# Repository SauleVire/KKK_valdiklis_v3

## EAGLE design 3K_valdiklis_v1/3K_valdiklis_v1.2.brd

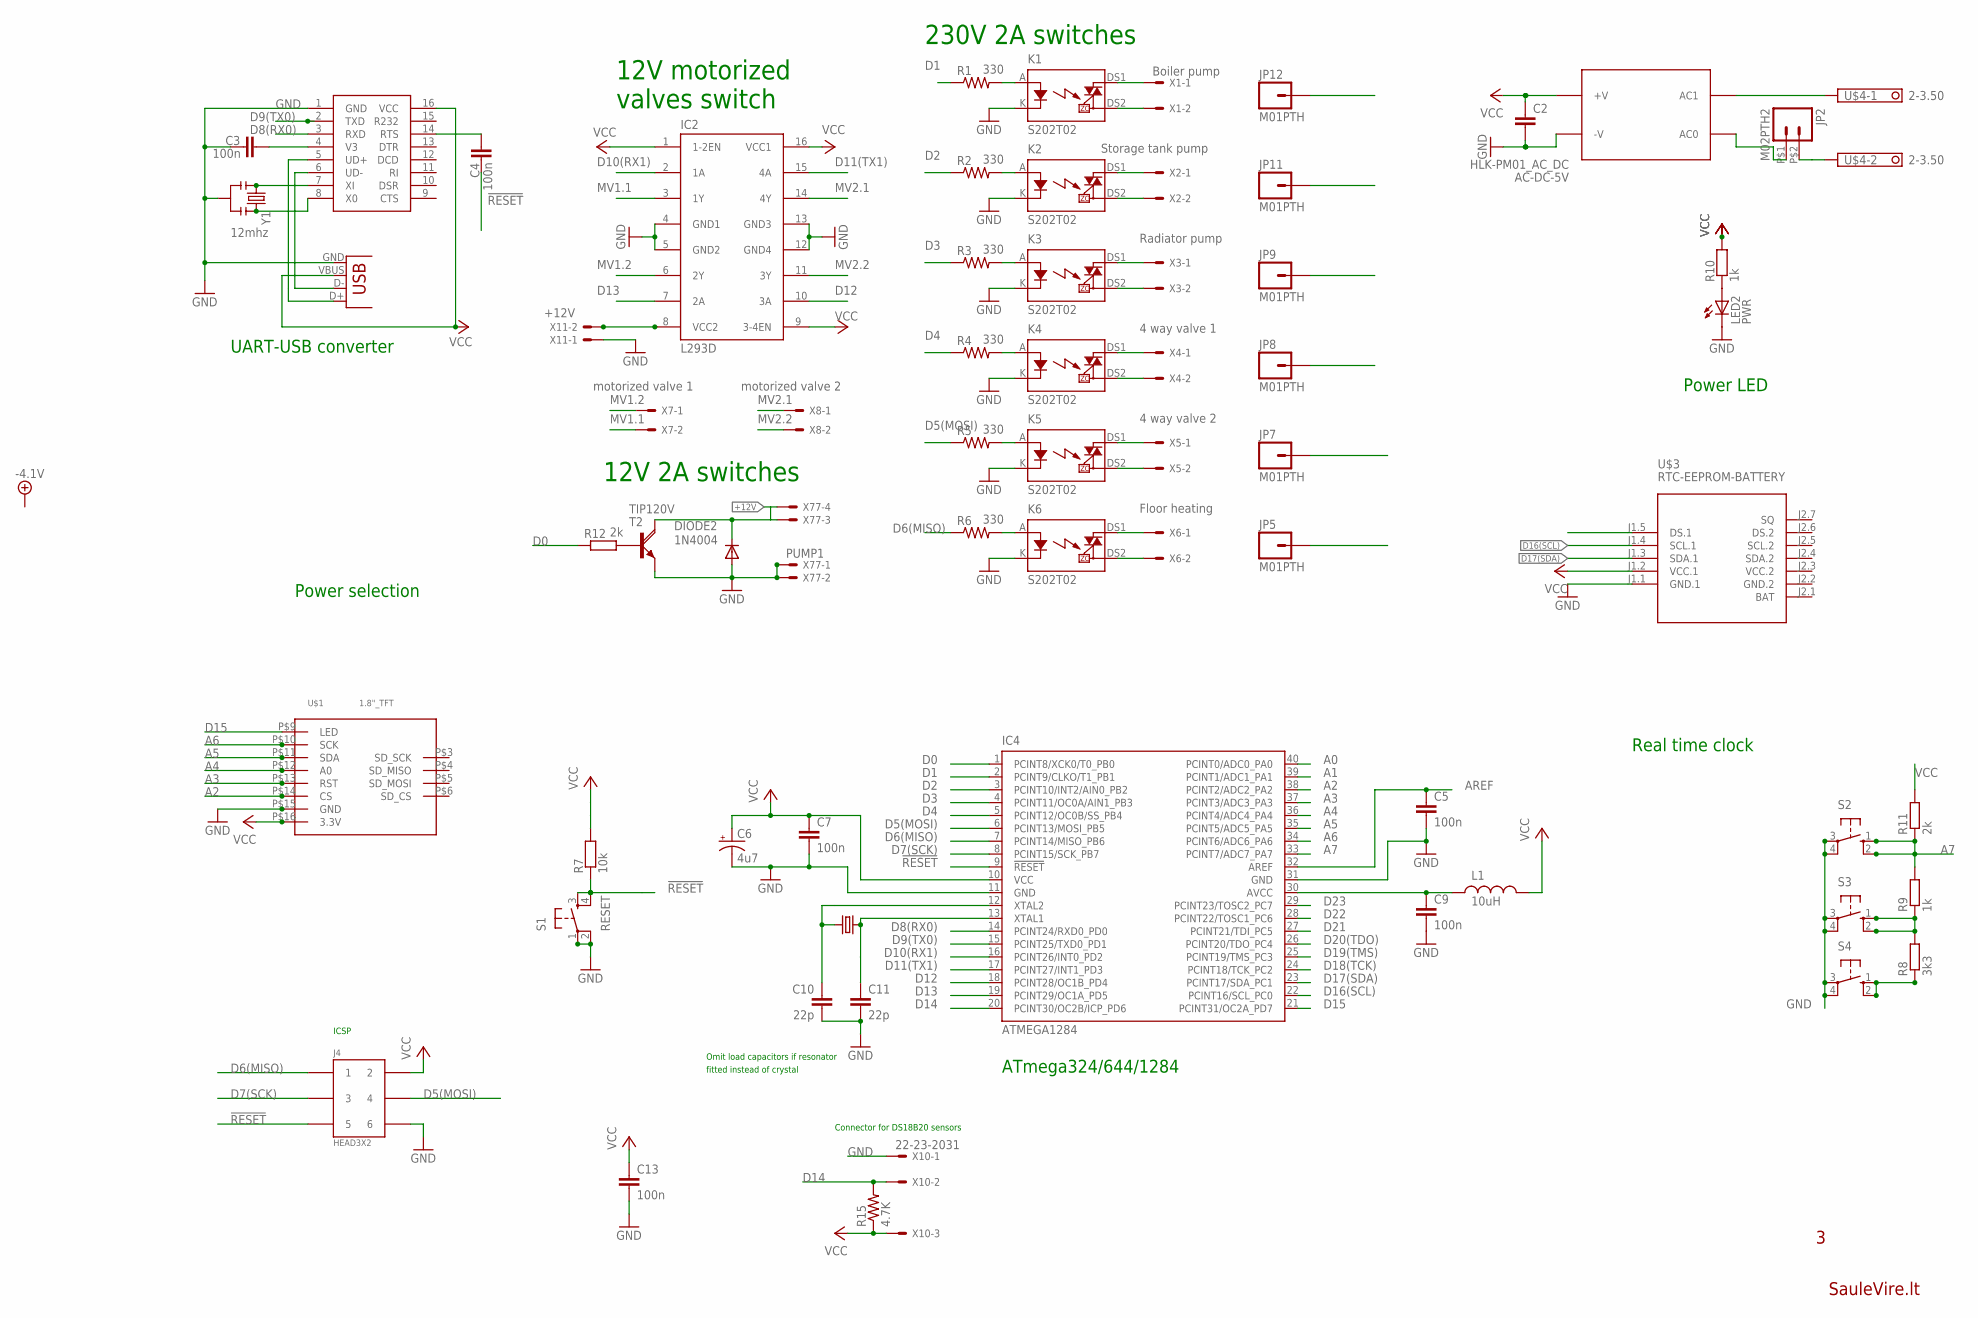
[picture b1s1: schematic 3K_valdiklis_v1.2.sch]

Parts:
AC-DC-5V: HLK-PM01_AC_DC
C2: C-EU025-024X044; C025-024X044
C3, C4, C5, C7, C9, C13: 100n; CAP-PTH-SMALL
C6: 4u7; CPOL-RADIAL-10UF-25V
C10, C11: 22p; CAP-PTH-SMALL
DIODE2: 1N4004; DO41-10
IC2: L293D; DIL16
IC4: ATMEGA1284; DIL40
J4: HEAD3X2
JP2: M02PTH2; 1X02_BIG
JP3: USB-B; USB-B-PTH
JP5, JP7, JP8, JP9, JP11, JP12: M01PTH; 1X01
K1, K2, K3, K4, K5, K6: S202T02
L1: 10uH; RES-AXIAL-0.4
LED2: PWR; LED3MM
R1, R2, R3, R4, R5, R6: 330; 0207/10
R7: 10k; RES-AXIAL-0.4
R8: 3k3; 0207/10
R9: 1k; 0207/10
R10: 1k; RES-AXIAL-0.4
R11, R12: 2k; 0207/10
R15: 4.7K; 0207/10
S1: RESET; TACTILE-PTH
S2, S3, S4: 10-XX; B3F-10XX
T2: TIP120V; TO220AV
U$1: 1.8"_TFT
U$2: CH340G; SO016
U$3: RTC-EEPROM-BATTERY; RTC_EEPROM_BATTERY
U$4: 2-3.50
X1: Boiler pump; 22-23-2021
X2: Storage tank pump; 22-23-2021
X3: Radiator pump; 22-23-2021
X4: 4 way valve 1; 22-23-2021
X5: 4 way valve 2; 22-23-2021
X6: Floor heating; 22-23-2021
X7: motorized valve 1; 22-23-2021
X8: motorized valve 2; 22-23-2021
X9: 16MHz; HC49US
X10: 22-23-2031
X11: +12V; 22-23-2021
X77: PUMP1; 22-23-2041
Y1: 12mhz; RESONATOR-PTH

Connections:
220V: AC-DC-5V.AC1, U$4.1
!RESET: C4.1, IC4.9 (!RESET), J4.5, R7.P$1 (1), S1.3, S1.4
+12V: DIODE2.C, T2.C, X77.3, X77.4
A0: IC4.40 (PCINT0/ADC0_PA0)
A1: IC4.39 (PCINT1/ADC1_PA1)
A2: IC4.38 (PCINT2/ADC2_PA2), U$1.P$14 (CS)
A3: IC4.37 (PCINT3/ADC3_PA3), U$1.P$13 (RST)
A4: IC4.36 (PCINT4/ADC4_PA4), U$1.P$12 (A0)
A5: IC4.35 (PCINT5/ADC5_PA5), U$1.P$11 (SDA)
A6: IC4.34 (PCINT6/ADC6_PA6), U$1.P$10 (SCK)
A7: IC4.33 (PCINT7/ADC7_PA7), R9.2, R11.1, S2.1 (S), S2.2 (S1)
AREF: C5.1, IC4.32 (AREF)
AVCC: C9.1, IC4.30 (AVCC), L1.P$1 (1)
D0: IC4.1 (PCINT8/XCK0/T0_PB0), R12.1
D1: IC4.2 (PCINT9/CLKO/T1_PB1), R1.1
D2: IC4.3 (PCINT10/INT2/AIN0_PB2), R2.1
D3: IC4.4 (PCINT11/OC0A/AIN1_PB3), R3.1
D4: IC4.5 (PCINT12/OC0B/SS_PB4), R4.1
D5(MOSI): IC4.6 (PCINT13/MOSI_PB5), J4.4, R5.1
D6(MISO): IC4.7 (PCINT14/MISO_PB6), J4.1, R6.1
D7(SCK): IC4.8 (PCINT15/SCK_PB7), J4.3
D8(RX0): IC4.14 (PCINT24/RXD0_PD0), U$2.3 (RXD)
D9(TX0): IC4.15 (PCINT25/TXD0_PD1), U$2.2 (TXD)
D10(RX1): IC2.2 (1A), IC4.16 (PCINT26/INT0_PD2)
D11(TX1): IC2.15 (4A), IC4.17 (PCINT27/INT1_PD3)
D12: IC2.10 (3A), IC4.18 (PCINT28/OC1B_PD4)
D13: IC2.7 (2A), IC4.19 (PCINT29/OC1A_PD5)
D14: IC4.20 (PCINT30/OC2B/ICP_PD6), R15.2, X10.2
D15: IC4.21 (PCINT31/OC2A_PD7), U$1.P$9 (LED)
D16(SCL): IC4.22 (PCINT16/SCL_PC0), U$3.J1.4 (SCL.1)
D17(SDA): IC4.23 (PCINT17/SDA_PC1), U$3.J1.3 (SDA.1)
D18(TCK): IC4.24 (PCINT18/TCK_PC2)
D19(TMS): IC4.25 (PCINT19/TMS_PC3)
D20(TDO): IC4.26 (PCINT20/TDO_PC4)
D21: IC4.27 (PCINT21/TDI_PC5)
D22: IC4.28 (PCINT22/TOSC1_PC6)
D23: IC4.29 (PCINT23/TOSC2_PC7)
GND: AC-DC-5V.-V, C2.2, C3.1, C5.2, C6.2 (-), C7.2, C9.2, C10.2, C11.2, C13.2, DIODE2.A, IC2.4 (GND1), IC2.5 (GND2), IC2.12 (GND4), IC2.13 (GND3), IC4.11 (GND), IC4.31 (GND), J4.6, JP3.GND, K1.K, K2.K, K3.K, K4.K, K5.K, K6.K, LED2.K (C), S1.1, S1.2, S2.3, S2.4 (P1), S3.3, S3.4 (P1), S4.3, S4.4 (P1), T2.E, U$1.P$15 (GND), U$2.1 (GND), U$3.J1.1 (GND.1), X10.1, X11.1, X77.1, X77.2, Y1.2
GND.2: U$3.J2.2 (GND.2)
MV1.1: IC2.3 (1Y), X7.2
MV1.2: IC2.6 (2Y), X7.1
MV2.1: IC2.14 (4Y), X8.1
MV2.2: IC2.11 (3Y), X8.2
unnamed: C11.1, IC4.13 (XTAL1), X9.1
unnamed: C10.1, IC4.12 (XTAL2), X9.2
unnamed: AC-DC-5V.AC0, JP2.P$1 (1)
unnamed: JP2.P$2 (2), U$4.2
unnamed: R8.1, S4.1 (S), S4.2 (S1)
unnamed: U$2.7 (XI), Y1.1
unnamed: LED2.A, R10.P$1 (1)
unnamed: U$2.8 (X0), Y1.3
unnamed: R8.2, R9.1, S3.1 (S), S3.2 (S1)
unnamed: C4.2, U$2.14 (RTS)
unnamed: JP3.D-, U$2.6 (UD-)
unnamed: R12.2, T2.B
unnamed: C3.2, U$2.4 (V3)
unnamed: K3.A, R3.2
unnamed: JP9.1, K3.DS1, X3.1
unnamed: IC2.8 (VCC2), X11.2
unnamed: JP3.D+, U$2.5 (UD+)
unnamed: K3.DS2, X3.2
unnamed: K2.A, R2.2
unnamed: JP11.1, K2.DS1, X2.1
unnamed: K2.DS2, X2.2
unnamed: K4.A, R4.2
unnamed: JP8.1, K4.DS1, X4.1
unnamed: K4.DS2, X4.2
unnamed: K1.A, R1.2
unnamed: JP12.1, K1.DS1, X1.1
unnamed: K1.DS2, X1.2
unnamed: K6.A, R6.2
unnamed: JP5.1, K6.DS1, X6.1
unnamed: K6.DS2, X6.2
unnamed: K5.A, R5.2
unnamed: JP7.1, K5.DS1, X5.1
unnamed: K5.DS2, X5.2
VCC: AC-DC-5V.+V, C2.1, C6.1 (+), C7.1, C13.1, IC2.1 (1-2EN), IC2.9 (3-4EN), IC2.16 (VCC1), IC4.10 (VCC), J4.2, JP3.VBUS, L1.P$2 (2), R7.P$2 (2), R10.P$2 (2), R11.2, R15.1, U$1.P$16 (3.3V), U$2.16 (VCC), U$3.J1.2 (VCC.1), X10.3
VCC.2: U$3.J2.3 (VCC.2)

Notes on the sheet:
Real time clock
ATmega324/644/1284
Power selection
Power LED
SauleVire.lt
Omit load capacitors if resonator
fitted instead of crystal
Connector for DS18B20 sensors
230V 2A switches
12V motorized valves switch
12V 2A switches
ICSP
UART-USB converter

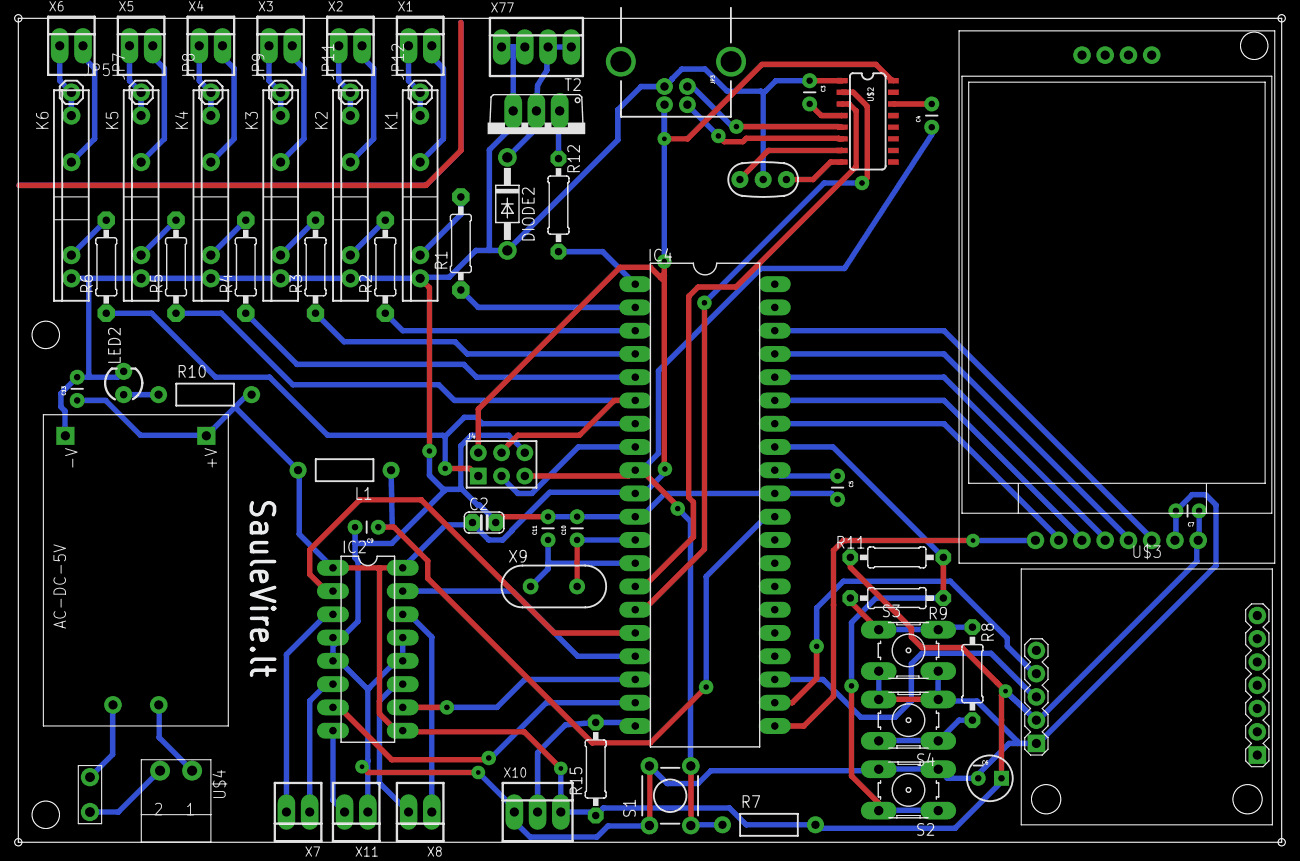
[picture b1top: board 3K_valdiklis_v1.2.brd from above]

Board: 2 copper layers, 138.0 x 90.0 mm, 66 parts (0 on the bottom side), 68 nets.

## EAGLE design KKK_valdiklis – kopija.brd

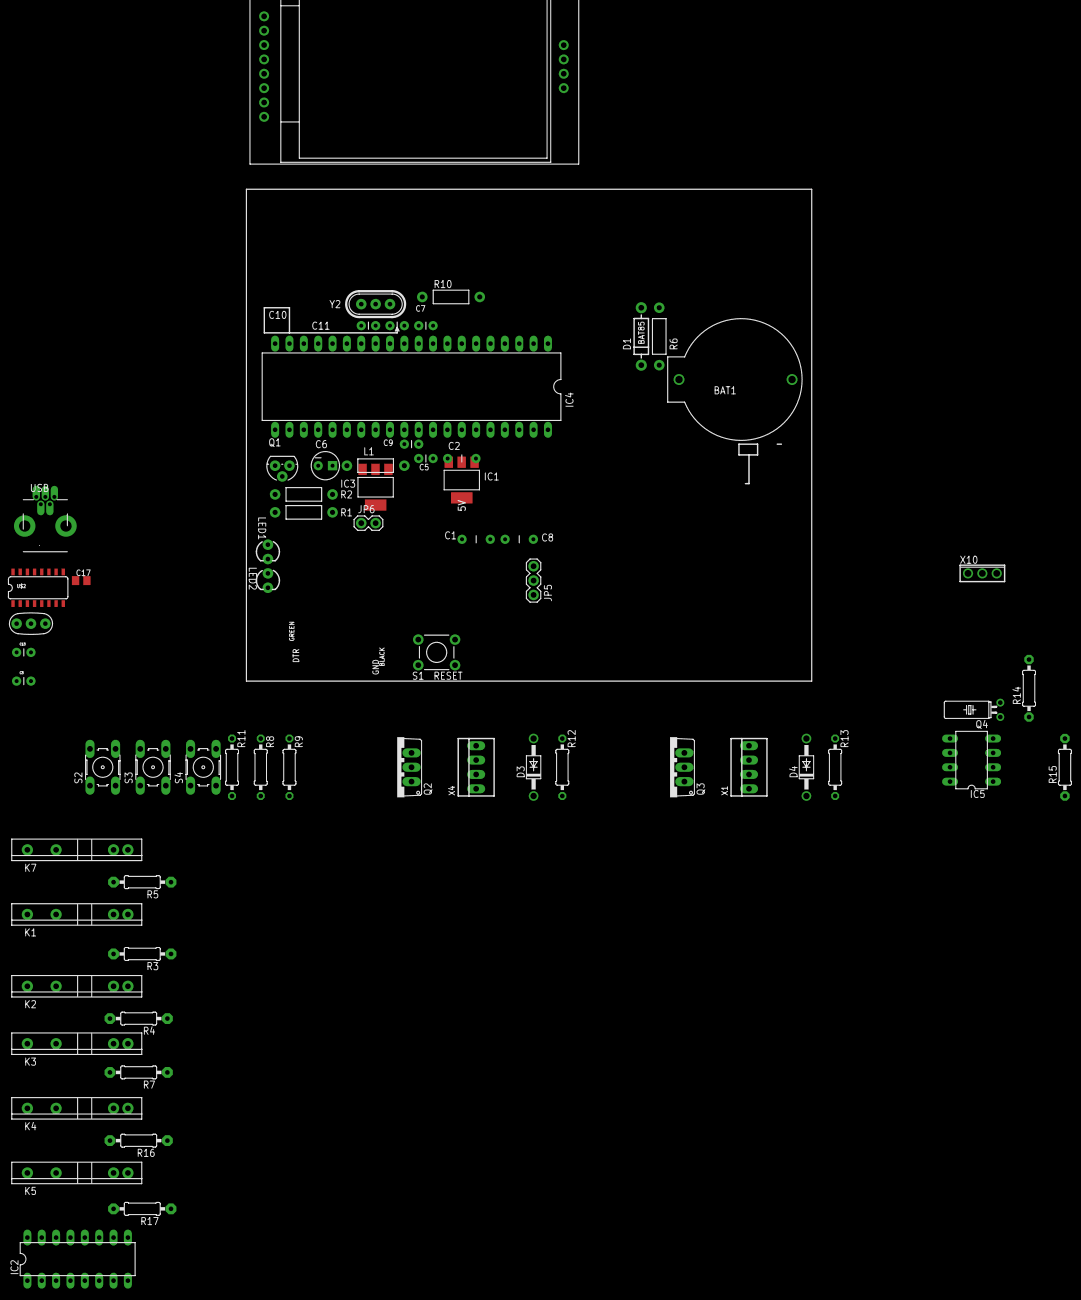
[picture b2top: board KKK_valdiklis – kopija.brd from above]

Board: 2 copper layers, 100.0 x 87.0 mm, 65 parts (0 on the bottom side), 45 nets, no tracks yet.

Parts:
BAT1: CR2032; BATTCOM_20MM_PTH
C1, C2, C8: 1u; CAP-PTH-5MM
C3, C5, C7, C9, C13: 100n; CAP-PTH-SMALL
C6: 4u7; CPOL-RADIAL-10UF-25V
C10, C11: 22p; CAP-PTH-SMALL
C17: 0.1uF; C0805K
D1: BAT85; DIODE-TH-0.4
D3, D4: 1N4004; DO41-10
IC1: MCP1702-3.3; SOT223
IC2: L293D; DIL16
IC3: MCP1702-5.0; SOT223
IC4: ATMEGA1284; DIL40
IC5: DS1307; DIL08
JP5: 3V3/5V; 1X03
JP6: VREG PWR; 1X02
K1, K2, K3, K4, K5, K7: S202T02
L1: 10uH; RES-AXIAL-0.4
LED1: D13; LED3MM
LED2: PWR; LED3MM
Q1: 2N7000; TO-92
Q2, Q3: TIP120V; TO220AV
Q4: 32.768; TC38H
R1, R2: 1k; RES-AXIAL-0.4
R3, R4, R5, R7, R16, R17: 330; 0207/10
R6: 10k; RES-AXIAL-0.4
R8: 3k3; 0207/10
R9: 1k; 0207/10
R10: 1M; RES-AXIAL-0.4
R11, R12, R13: 2k; 0207/10
R14: 2.2K; 0207/10
R15: 2.2k; 0207/10
S1: RESET; TACTILE-PTH
S2, S3, S4: B3F-10XX
U$1: 1.8"_TFT
U$2: CH340G; SO016
USB: USB-MINIB-THM-MOLEX
X1, X4: PUMP; 22-23-2041
X10: 3POL254
Y1: 12mhz; RESONATOR-PTH
Y2: 16MHz; HC49U-V-RESONATOR

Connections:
13(SCK): Q1.2, R10.P$2
20(SDA): IC5.5, R15.1
21(SCL): IC5.6, R14.2
!RESET: C17.2, D1.A, IC4.9, R6.P$1, S1.3, S1.4
+3V3: C2.1, IC1.2, JP5.1
+5V: C1.1, IC1.3, JP5.3, JP6.2, U$2.16, USB.VBUS, X10.3
A0: IC4.40, R9.2, R11.1, S2.1, S2.2
AREF: C5.1, IC4.32
AVCC: C9.1, IC4.30, L1.P$1
D0: IC4.1, R5.1
D1: IC4.2, R17.1
D2: IC4.3, R16.1, X10.2
D3: IC4.4, R7.1, R12.1, R13.1
D4: IC4.5, R4.1
GND: BAT1.2, C1.2, C2.2, C3.1, C5.2, C6.2, C7.2, C8.2, C9.2, C10.2, C11.2, C13.2, D3.A, IC1.1, IC3.1, IC4.11, IC4.31, IC5.4, K1.K, K2.K, K3.K, K4.K, K5.K, K7.K, LED2.K, Q1.1, Q2.E, R10.P$1, S1.1, S1.2, S2.3, S2.4, S3.3, S3.4, S4.3, S4.4, U$2.1, USB.GND, USB.ID, X4.3, X4.4, X10.1, Y1.2, Y2.GND
GND1: D4.A, IC2.4, Q3.E, X1.3, X1.4
unnamed: C11.1, IC4.13, Y2.2
unnamed: C10.1, IC4.12, Y2.1
unnamed: LED1.A, R1.P$1
unnamed: LED1.K, Q1.3
unnamed: U$2.7, Y1.1
unnamed: R8.1, S4.1, S4.2
unnamed: C3.2, U$2.4
unnamed: LED2.A, R2.P$1
unnamed: U$2.8, Y1.3
unnamed: R8.2, R9.1, S3.1, S3.2
unnamed: C17.1, U$2.14
unnamed: U$2.6, USB.D-
unnamed: Q2.B, R12.2
unnamed: IC3.2, JP6.1
unnamed: D3.C, Q2.C, X4.1, X4.2
unnamed: K1.A, R3.2
unnamed: Q3.B, R13.2
unnamed: D4.C, Q3.C, X1.1, X1.2
unnamed: IC5.1, Q4.2
unnamed: IC5.2, Q4.1
unnamed: U$2.5, USB.D+
unnamed: K2.A, R4.2
unnamed: BAT1.1, IC5.3
unnamed: K7.A, R5.2
unnamed: K3.A, R7.2
unnamed: K4.A, R16.2
unnamed: K5.A, R17.2
VCC: C6.1, C7.1, C13.1, D1.C, IC4.10, IC5.8, JP5.2, L1.P$2, R1.P$2, R2.P$2, R6.P$2, R11.2, R14.1, R15.2
VIN: C8.1, IC3.3

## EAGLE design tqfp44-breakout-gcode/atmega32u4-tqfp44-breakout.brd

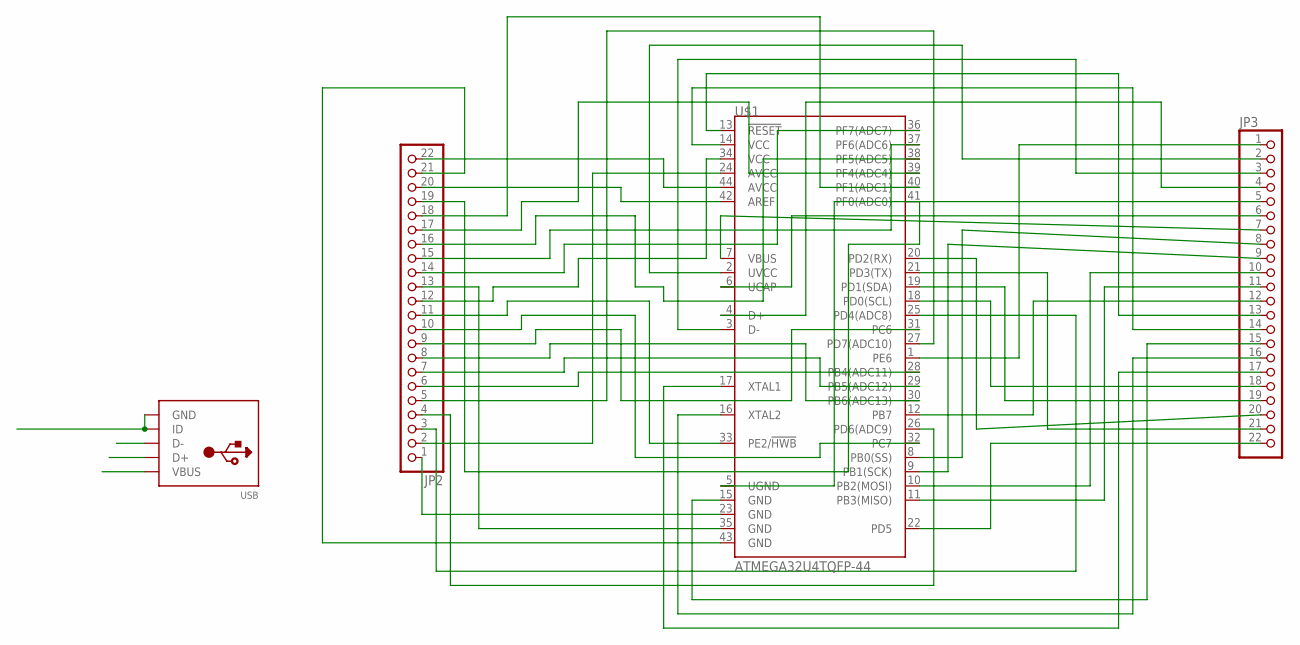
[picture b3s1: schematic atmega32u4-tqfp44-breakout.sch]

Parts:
JP2, JP3: PINHD-1X22; 1X22
U$1: ATMEGA32U4TQFP-44; TQFP44
USB: USB-MINIB-THM-MOLEX

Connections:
D+: JP3.4, U$1.4 (D+)
D-: JP3.3, U$1.3 (D-)
GND1: USB.GND, USB.ID
unnamed: JP3.1, U$1.1 (PE6)
unnamed: JP2.2, U$1.24 (AVCC)
unnamed: JP3.5, U$1.5 (UGND)
unnamed: JP3.6, U$1.6 (UCAP)
unnamed: JP3.7, U$1.7 (VBUS)
unnamed: JP3.8, U$1.8 (PB0(SS))
unnamed: JP3.9, U$1.9 (PB1(SCK))
unnamed: JP3.10, U$1.10 (PB2(MOSI))
unnamed: JP3.11, U$1.11 (PB3(MISO))
unnamed: JP3.12, U$1.12 (PB7)
unnamed: JP3.13, U$1.13 (!RESET)
unnamed: JP3.14, U$1.14 (VCC)
unnamed: JP3.15, U$1.15 (GND)
unnamed: JP3.16, U$1.16 (XTAL2)
unnamed: JP3.17, U$1.17 (XTAL1)
unnamed: JP3.18, U$1.18 (PD0(SCL))
unnamed: JP3.19, U$1.19 (PD1(SDA))
unnamed: JP3.20, U$1.20 (PD2(RX))
unnamed: JP3.21, U$1.21 (PD3(TX))
unnamed: JP3.22, U$1.22 (PD5), USB.D-
unnamed: JP2.1, U$1.23 (GND), USB.D+
unnamed: JP2.22, U$1.44 (AVCC)
unnamed: JP2.3, U$1.25 (PD4(ADC8))
unnamed: JP3.2, U$1.2 (UVCC)
unnamed: JP2.4, U$1.26 (PD6(ADC9))
unnamed: JP2.5, U$1.27 (PD7(ADC10))
unnamed: JP2.6, U$1.28 (PB4(ADC11))
unnamed: JP2.7, U$1.29 (PB5(ADC12))
unnamed: JP2.8, U$1.30 (PB6(ADC13))
unnamed: JP2.9, U$1.31 (PC6)
unnamed: JP2.10, U$1.32 (PC7)
unnamed: JP2.11, U$1.33 (PE2/!HWB)
unnamed: JP2.12, U$1.34 (VCC)
unnamed: JP2.13, U$1.35 (GND)
unnamed: JP2.14, U$1.36 (PF7(ADC7))
unnamed: JP2.15, U$1.37 (PF6(ADC6))
unnamed: JP2.16, U$1.38 (PF5(ADC5))
unnamed: JP2.17, U$1.39 (PF4(ADC4))
unnamed: JP2.18, U$1.40 (PF1(ADC1))
unnamed: JP2.19, U$1.41 (PF0(ADC0))
unnamed: JP2.20, U$1.42 (AREF)
unnamed: JP2.21, U$1.43 (GND)
VCC: USB.VBUS

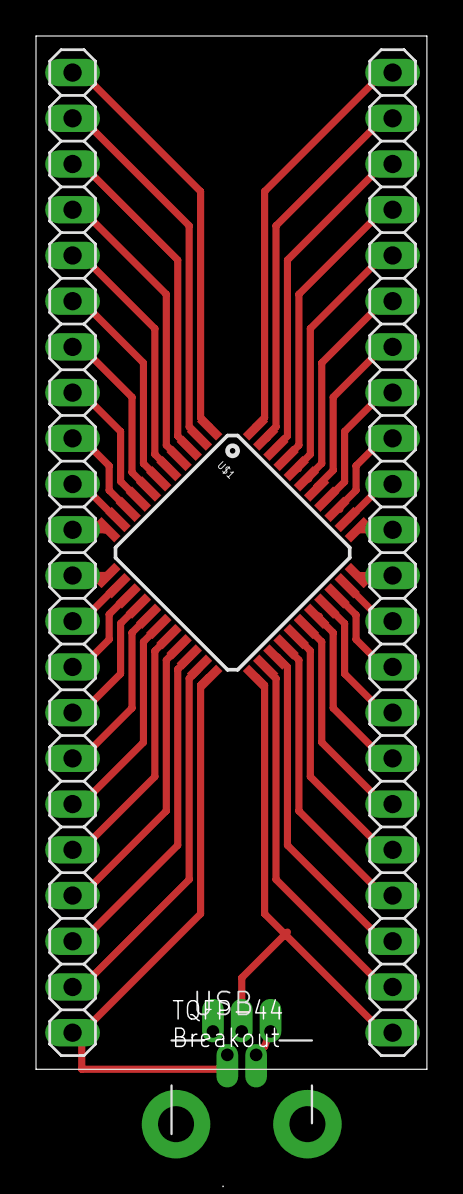
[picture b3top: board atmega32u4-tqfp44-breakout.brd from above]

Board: 2 copper layers, 21.7 x 57.4 mm, 4 parts (0 on the bottom side), 45 nets.

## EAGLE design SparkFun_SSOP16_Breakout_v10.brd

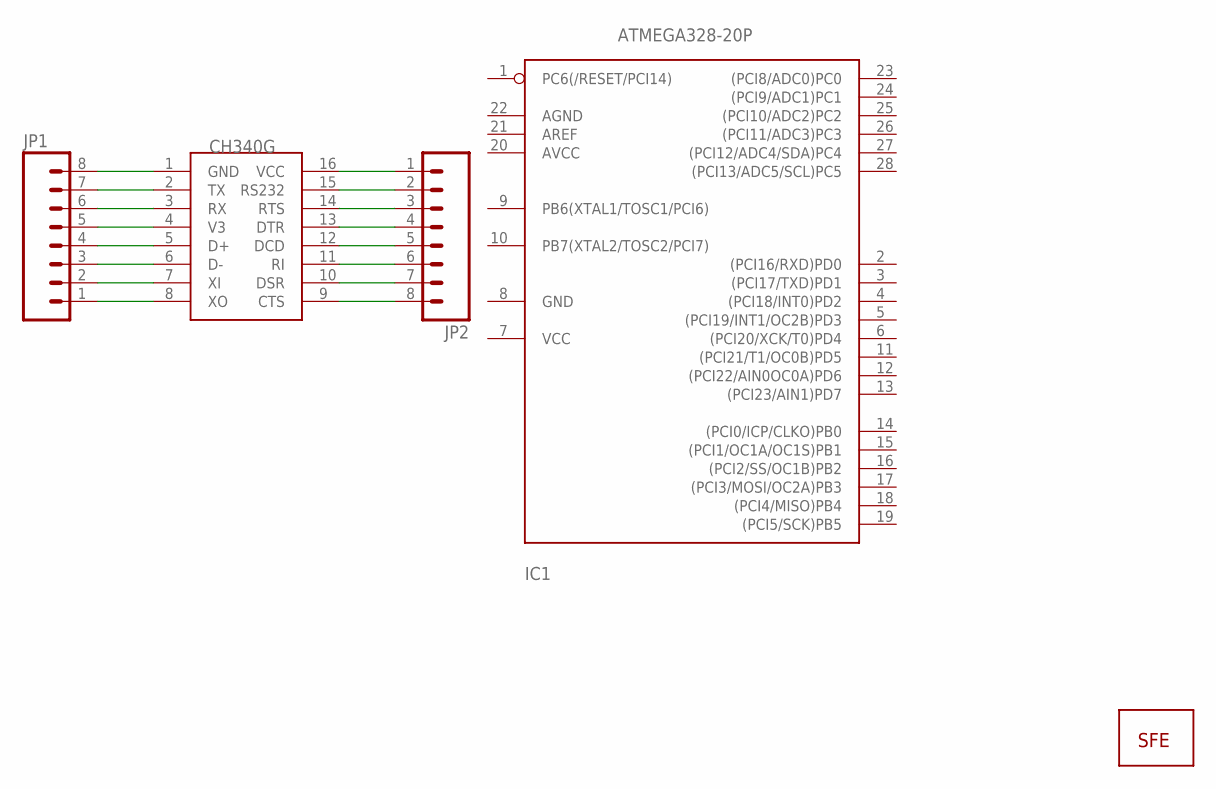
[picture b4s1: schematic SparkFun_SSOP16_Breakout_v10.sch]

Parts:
IC1: ATMEGA328-20P; DIL28-3
JP1, JP2: M08; 1X08
U$1: LOGO-SFESK; SFE-LOGO-FLAME
U$2: CH340G; SOIC16

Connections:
unnamed: JP1.1, U$2.8 (XO)
unnamed: JP1.2, U$2.7 (XI)
unnamed: JP1.3, U$2.6 (D-)
unnamed: JP1.4, U$2.5 (D+)
unnamed: JP1.5, U$2.4 (V3)
unnamed: JP1.6, U$2.3 (RX)
unnamed: JP1.7, U$2.2 (TX)
unnamed: JP1.8, U$2.1 (GND)
unnamed: JP2.1, U$2.16 (VCC)
unnamed: JP2.2, U$2.15 (RS232)
unnamed: JP2.3, U$2.14 (RTS)
unnamed: JP2.4, U$2.13 (DTR)
unnamed: JP2.5, U$2.12 (DCD)
unnamed: JP2.6, U$2.11 (RI)
unnamed: JP2.7, U$2.10 (DSR)
unnamed: JP2.8, U$2.9 (CTS)

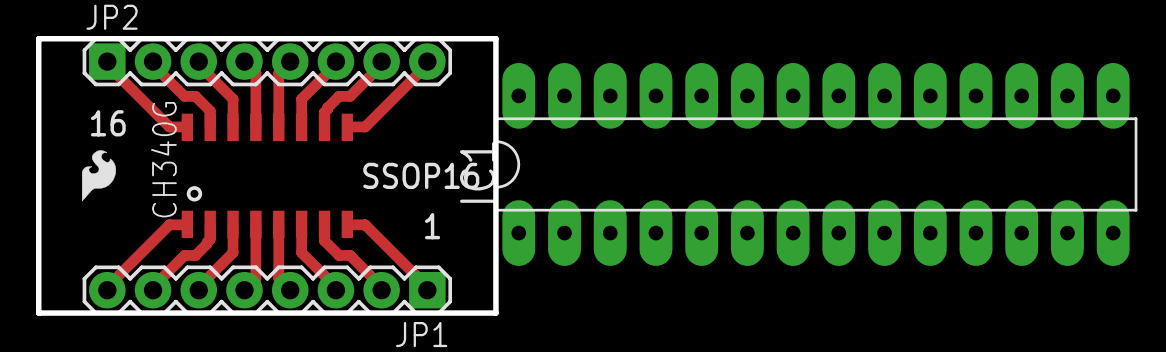
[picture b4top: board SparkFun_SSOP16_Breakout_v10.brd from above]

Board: 2 copper layers, 25.4 x 15.2 mm, 5 parts (0 on the bottom side), 16 nets.

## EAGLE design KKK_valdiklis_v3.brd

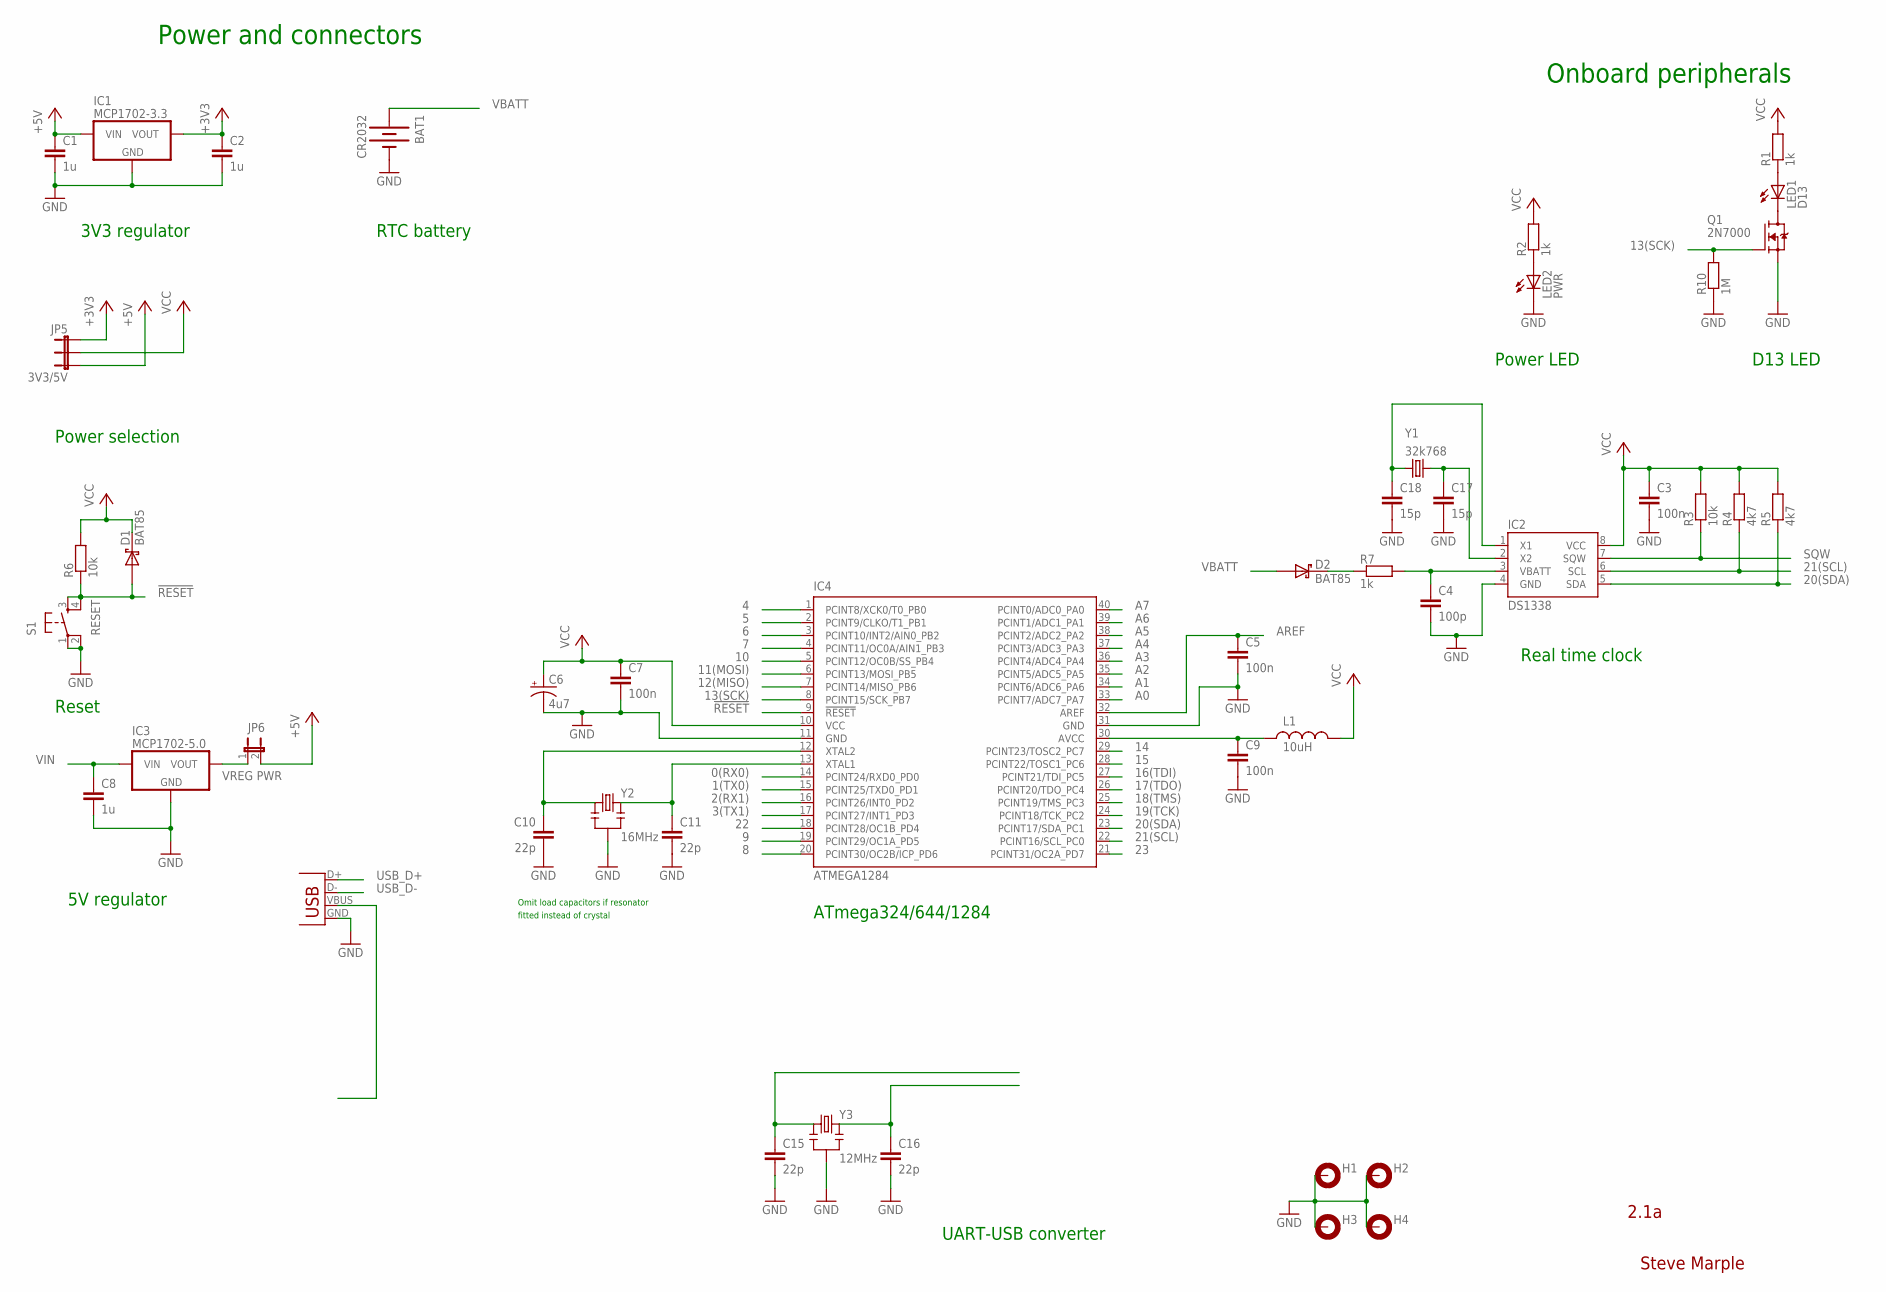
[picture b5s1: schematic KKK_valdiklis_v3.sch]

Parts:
BAT1: CR2032; BATTCOM_20MM_PTH
C1, C2, C8: 1u; CAP-PTH-5MM
C3, C5, C7, C9: 100n; CAP-PTH-SMALL
C4: 100p; CAP-PTH-SMALL
C6: 4u7; CPOL-RADIAL-10UF-25V
C10, C11, C15, C16: 22p; CAP-PTH-SMALL
C17, C18: 15p; CAP-PTH-SMALL
D1, D2: BAT85; DIODE-TH-0.4
H1, H2, H3, H4: MOUNT-PAD-ROUND3.0; 3,0-PAD
IC1: MCP1702-3.3; TO-92
IC2: DS1338; SO08
IC3: MCP1702-5.0; TO-92
IC4: ATMEGA1284; DIL40
JP5: 3V3/5V; 1X03
JP6: VREG PWR; 1X02
L1: 10uH; RES-AXIAL-0.4
LED1: D13; LED3MM
LED2: PWR; LED3MM
Q1: 2N7000; TO-92
R1, R2, R7: 1k; RES-AXIAL-0.4
R3, R6: 10k; RES-AXIAL-0.4
R4, R5: 4k7; RES-AXIAL-0.4
R10: 1M; RES-AXIAL-0.4
S1: RESET; TACTILE-PTH
X3: USB; USB-B-PTH
Y1: 32k768; TC38H
Y2: 16MHz; HC49U-V-RESONATOR
Y3: 12MHz; HC49U-V-RESONATOR

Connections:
0(RX0): IC4.14 (PCINT24/RXD0_PD0)
1(TX0): IC4.15 (PCINT25/TXD0_PD1)
2(RX1): IC4.16 (PCINT26/INT0_PD2)
3(TX1): IC4.17 (PCINT27/INT1_PD3)
4: IC4.1 (PCINT8/XCK0/T0_PB0)
5: IC4.2 (PCINT9/CLKO/T1_PB1)
6: IC4.3 (PCINT10/INT2/AIN0_PB2)
7: IC4.4 (PCINT11/OC0A/AIN1_PB3)
8: IC4.20 (PCINT30/OC2B/ICP_PD6)
9: IC4.19 (PCINT29/OC1A_PD5)
10: IC4.5 (PCINT12/OC0B/SS_PB4)
11(MOSI): IC4.6 (PCINT13/MOSI_PB5)
12(MISO): IC4.7 (PCINT14/MISO_PB6)
13(SCK): IC4.8 (PCINT15/SCK_PB7), Q1.2 (G), R10.P$2 (2)
14: IC4.29 (PCINT23/TOSC2_PC7)
15: IC4.28 (PCINT22/TOSC1_PC6)
16(TDI): IC4.27 (PCINT21/TDI_PC5)
17(TDO): IC4.26 (PCINT20/TDO_PC4)
18(TMS): IC4.25 (PCINT19/TMS_PC3)
19(TCK): IC4.24 (PCINT18/TCK_PC2)
20(SDA): IC2.5 (SDA), IC4.23 (PCINT17/SDA_PC1), R5.P$1 (1)
21(SCL): IC2.6 (SCL), IC4.22 (PCINT16/SCL_PC0), R4.P$1 (1)
22: IC4.18 (PCINT28/OC1B_PD4)
23: IC4.21 (PCINT31/OC2A_PD7)
!RESET: D1.A, IC4.9 (!RESET), R6.P$1 (1), S1.3, S1.4
+3V3: C2.1, IC1.3 (VOUT), JP5.1
+5V: C1.1, IC1.2 (VIN), JP5.3, JP6.2
A0: IC4.33 (PCINT7/ADC7_PA7)
A1: IC4.34 (PCINT6/ADC6_PA6)
A2: IC4.35 (PCINT5/ADC5_PA5)
A3: IC4.36 (PCINT4/ADC4_PA4)
A4: IC4.37 (PCINT3/ADC3_PA3)
A5: IC4.38 (PCINT2/ADC2_PA2)
A6: IC4.39 (PCINT1/ADC1_PA1)
A7: IC4.40 (PCINT0/ADC0_PA0)
AREF: C5.1, IC4.32 (AREF)
AVCC: C9.1, IC4.30 (AVCC), L1.P$1 (1)
GND: BAT1.2 (-), C1.2, C2.2, C3.2, C4.2, C5.2, C6.2 (-), C7.2, C8.2, C9.2, C10.2, C11.2, C15.2, C16.2, C17.2, C18.2, H1.B3,0, H2.B3,0, H3.B3,0, H4.B3,0, IC1.1 (GND), IC2.4 (GND), IC3.1 (GND), IC4.11 (GND), IC4.31 (GND), LED2.K (C), Q1.1 (S), R10.P$1 (1), S1.1, S1.2, X3.GND, Y2.GND (2), Y3.GND (2)
unnamed: C11.1, IC4.13 (XTAL1), Y2.2 (3)
unnamed: C10.1, IC4.12 (XTAL2), Y2.1
unnamed: LED1.A, R1.P$1 (1)
unnamed: LED1.K (C), Q1.3 (D)
unnamed: C18.1, IC2.1 (X1), Y1.2
unnamed: C16.1, Y3.2 (3)
unnamed: LED2.A, R2.P$1 (1)
unnamed: D2.C, R7.P$1 (1)
unnamed: C4.1, IC2.3 (VBATT), R7.P$2 (2)
unnamed: C17.1, IC2.2 (X2), Y1.1
unnamed: IC3.3 (VOUT), JP6.1
unnamed: C15.1, Y3.1
SQW: IC2.7 (SQW), R3.P$1 (1)
USB_D+: X3.D+
USB_D-: X3.D-
VBATT: BAT1.1 (+), D2.A
VCC: C3.1, C6.1 (+), C7.1, D1.C, IC2.8 (VCC), IC4.10 (VCC), JP5.2, L1.P$2 (2), R1.P$2 (2), R2.P$2 (2), R3.P$2 (2), R4.P$2 (2), R5.P$2 (2), R6.P$2 (2)
VIN: C8.1, IC3.2 (VIN)

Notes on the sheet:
Power and connectors
Onboard peripherals
Real time clock
ATmega324/644/1284
D13 LED
Reset
Power selection
3V3 regulator
RTC battery
Power LED
Steve Marple
2.1a
5V regulator
Omit load capacitors if resonator
fitted instead of crystal
UART-USB converter

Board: 2 copper layers, 45 parts (0 on the bottom side), 25 nets, no tracks yet.

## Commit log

2016-09-25 pakeitimai
    reilės keičiamos optoporomis, važtuvams valdyti bus naudojama L293D,
    visi D18B20 bus jungiami ant vieno kontakto
2016-09-26 eiga...
2016-09-26 projektavimas
2016-10-03 trasavimas
2016-10-06 trasavimas, išmesta ch340
2016-10-16 trasavimas
    be klaidų!!

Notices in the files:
KKK_valdiklis_v3.brd:
License: Creative Commons Attribution
Copyright Steve Marple 2012
parts and their libraries:
tft_1.8_1.44_oled_0.96: Released under the Creative Commons Attribution 4.0 International License: http://creativecommons.org/licenses/by/4.0
SparkFun-Connectors-1: Licensing: CC v3.0 Share-Alike You are welcome to use this library for commercial purposes.
